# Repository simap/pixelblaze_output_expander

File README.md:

# USE THE APPROPRIATE BRANCH FOR YOUR HARDWARE VERSION!

* v1.x: https://github.com/simap/pixelblaze_output_expander/tree/master
* v2.x: https://github.com/simap/pixelblaze_output_expander/tree/v2.x
* v3.x: https://github.com/simap/pixelblaze_output_expander/tree/v3.x
* v4.x: this branch

The v3.x_spi and v3.x_apa102fastdata branches are variant firmwares for v3 boards. Both features are incorporated into v4.

Pixelblaze Output Expander Board
-------------------

This is a UART (serial) or SPI driven WS2811/WS2812/WS2813/NeoPixel and APA102/SK9822/DotStar driver. It receives frame data from another microcontroller, buffers it per channel, handles color ordering, and outputs up to 8 channels with level shifting to 5v. WS2812 and APA102 type LEDs can be mixed across channels.

Its primarily designed as an output expander for [Pixelblaze](https://www.tindie.com/products/12158/), but can be used with any microcontroller that can output 2Mbps serial or SPI. The UART input doesn't need to sustain 2Mbps, so this should work even for software serial implementations as long as the microcontroller is capable of outputting single characters at this rate.

See the companion [Arduino Library Driver](https://github.com/simap/pbDriverAdapter/) for use with Arduinos.

This branch is the firmware for the v4 boards, which are based on the RP2350. It also runs on RP2350 dev boards. The STM32 based v1 to v3 boards each have their own branch, linked above. The protocol is the same across all of them, the v4 boards add SPI input, larger buffers, and firmware updates over the data line.

| | v1 | v2 | v3 | v4 |
|---|---|---|---|---|
| MCU | STM32F070 | STM32F103 | STM32L432 | RP2350 |
| Input | UART 2Mbps | UART 2Mbps | UART 2Mbps | UART 2Mbps or SPI up to 20MHz |
| Bytes per channel | 720 | 2408 | 4808 | 16008 |
| WS2812 RGB pixels per channel | 240 | 802 | 1602 | 5336 |
| APA102 pixels per channel | no | 600 | 1200 | 4000 |

Input
-------------------

The data input pin takes either UART or SPI. Both receivers run all the time and the board picks whichever is active.

UART is 8N1 at 2Mbps, same as earlier boards. Only the data line is used.

SPI uses the clock input pin plus the data pin. There is no chip select. Mode 0 (clock idles low, data sampled on the rising edge), MSB first, any clock from 500kHz to 20MHz. The sender doesn't have to be continuous, bytes can arrive at any pace. If the clock stops for 10us in the middle of a byte, the partial byte is dropped and the receiver realigns on the next clock edge, so a sender should leave at least a 20us gap before each set of frames to recover from a lost or extra clock edge.

Once 8 bytes have arrived over SPI, the board switches to SPI and ignores the UART input (which sees the shared data line toggling at SPI rates). After 1 second with no SPI clock it switches back to UART.

Data Frame Format
-------------------

Frames start with a magic 4-byte sequence, followed by the channel ID (8 bits), then the command type (8 bits). Some commands have additional header/structs and payloads, finally every frame is ended with a 32-bit CRC that covers the entire frame (from magic to the last byte before CRC). All multi-byte fields are little endian.

```c
typedef struct {
	int8_t magic[4]; //"UPXL"
	uint8_t channel;
	uint8_t recordType; //set channel ws2812 opts+data, draw all
} PBFrameHeader;
```

Six commands are implemented. Four set a channel's configuration and buffer data, one draws all channels, and one carries a firmware update:

```c
enum {
	SET_CHANNEL_WS2812 = 1, DRAW_ALL, SET_CHANNEL_APA102_DATA, SET_CHANNEL_APA102_CLOCK, SET_CHANNEL_APA102_FAST_DATA, UPDATE
} RecordType;
```

The channel ID is part of the PBFrameHeader. Each board supports 8 channels, and has an additional 3 bits of address configured by cuttable jumpers on the underside of the board. Up to 64 channels can be on the same bus (8 boards w/ 8 channels each). The low 3 bits pick the channel on the board, the upper 3 bits must match the board's jumpers or the frame is ignored.

Any `SET_CHANNEL_*` command with a `pixels` count of 0 disables that channel.

### `SET_CHANNEL_WS2812`

The `SET_CHANNEL_WS2812` command frame header is immediately followed by a structure defining the configuration for that channel, and then followed by RGB or RGBW pixel data:

```c
typedef struct {
	uint8_t numElements; //3 (RGB) or 4 (RGBW)
	uint8_t redIndex :2, greenIndex :2, blueIndex :2, whiteIndex :2; //color orders, data on the line assumed to be RGB or RGBW
	uint16_t pixels;
} PBChannel;
```

In total:

```
PBFrameHeader + PBChannel + bytes[numElements * pixels] + CRC
```

Output is always at 800KHz.

### `SET_CHANNEL_APA102_DATA`

Sets a channel as the data line for APA102 type LEDs. Pixel data on the line is 4 bytes per pixel, RGB followed by a 5-bit brightness value. The color order bits work like WS2812. The start and end frames are added by the board, don't send them.

```c
typedef struct {
	uint32_t frequency; //clock rate in Hz
	uint8_t redIndex :2, greenIndex :2, blueIndex :2, unused :2;
	uint8_t reserved;
	uint16_t pixels;
} PBAPA102DataChannel;
```

In total:

```
PBFrameHeader + PBAPA102DataChannel + bytes[4 * pixels] + CRC
```

### `SET_CHANNEL_APA102_CLOCK`

Sets a channel as the clock line for APA102 type LEDs. Any number of data channels can share one clock channel, the clock runs for as many bits as the longest APA102 data channel on the board.

```c
typedef struct {
	uint32_t frequency; //clock rate in Hz
} PBAPA102ClockChannel;
```

In total:

```
PBFrameHeader + PBAPA102ClockChannel + CRC
```

The clock and all data channels are started together from the same clock divider so they stay in step. If channels ask for different frequencies, all APA102 channels on the board run at the lowest one requested, limited to the range 10KHz to 20MHz.

### `SET_CHANNEL_APA102_FAST_DATA`

Same as `SET_CHANNEL_APA102_DATA` but pixel data on the line is 2 bytes per pixel in RGB565, little endian. This halves the input bandwidth for more FPS. The board expands each pixel with a gamma curve, then uses the APA102's 5-bit brightness value to keep some dynamic range in the dark end.

```c
typedef struct {
	uint32_t frequency; //clock rate in Hz
	uint8_t redIndex :2, greenIndex :2, blueIndex :2, unused :2;
	uint8_t gammaTenths; //gamma * 10, 10 to 25 (1.0 to 2.5)
	uint16_t pixels;
} PBAPA102FastDataChannel;
```

In total:

```
PBFrameHeader + PBAPA102FastDataChannel + bytes[2 * pixels] + CRC
```

### `DRAW_ALL`

The `DRAW_ALL` command ignores the channel from the frame header, though it must still be followed by a CRC. All channels on the bus are drawn simultaneously when this command is received. This command ignores channel ID.

In total:

```
PBFrameHeader + CRC
```

### `UPDATE` (v4 boards)

Record type 6 carries a firmware update payload for the RP2350 based v4 boards. It is broadcast, so the channel byte is ignored. The frame header is followed by this header, then the payload, then the usual frame CRC:

```c
typedef struct {
	char key[64];     // hardware and payload type, NUL padded, e.g. "RP2350_ARM-2MB-standard-firmware"
	uint32_t length;  // payload bytes
	uint32_t crc;     // CRC32 of just key and length
} PBUpdate;
```

A board accepts the record only if the key is the one it was built with, so updates for other boards on the same bus are consumed and ignored. The header CRC keeps a magic sequence that happens to appear inside pixel data from locking up the parser on a bogus multi-megabyte payload. The payload is the `outputexpander.bin` from the build, which the pico-sdk seals with a SHA-256. See Firmware Updates below for what happens on the board.

Error Handling
-------------------

The firmware is designed to tolerate noise and data errors. Channel data is double-buffered. Each `SET_CHANNEL_*` frame is received into a spare buffer and only becomes the channel's pending frame once its CRC checks out. `DRAW_ALL` swaps every pending frame in and draws. A CRC mismatch throws the frame out and the channel keeps drawing its last good frame, so LEDs never see corrupted or zeroed data. Frames received during a draw go into a different buffer than the one being drawn.

The magic header provides a way to align frames in case of continuous transmission.

It's assumed that data will be more or less continuously flowing, and the reception code doesn't timeout if the input goes idle.

If part of a frame is received, it will wait for enough data to complete that frame, and eventually throw that out if the CRC doesn't match. If that is in the middle of another frame, it will discard data until the magic frame start sequence is found.

Frames with a bad or impossible header (unknown record type, more pixels than fit in a channel, zero frequency, etc) are skipped a byte at a time until the next magic sequence.

Timing Considerations
-------------------

Since channel data is double-buffered, you can send the next frame's channel data as soon as `DRAW_ALL` has been sent, while the previous frame is still going out to the LEDs.

A `DRAW_ALL` that arrives while a draw is still in progress is dropped. The same goes for a `DRAW_ALL` within 300us of the end of a WS2812 draw, since the LEDs need that time to latch. The channel data sent before it is kept and goes out on the next `DRAW_ALL`. WS2812 output takes 30us per RGB pixel (40us for RGBW) on the longest channel, plus the 300us latch, so for example 300 RGB pixels takes about 9.3ms and tops out around 107 FPS. APA102 takes 32 bits per pixel plus start and end frames at the configured clock rate.

Each channel only sends as many pixels as it was configured for, so a short channel finishes early and doesn't wait for the longest.

Status LEDs
-------------------

The status LED is on solid while frames are arriving, and breathes slowly when the input has been idle for a second. The draw LED is on while valid channel data and draw commands are both arriving.

Firmware Updates
-------------------

v4 boards can be updated over the data line with the `UPDATE` record. Flash is split into an A/B pair of 384KB slots with a partition table in the first sector. An update is written to whichever slot isn't running, then the board reboots into it. The bootrom checks the SHA-256 before running it, and falls back to the old slot if it doesn't check out, if power is lost mid-write, or if the new firmware never starts working.

The new firmware runs in try-before-you-buy mode. It commits itself (and the bootrom erases the old slot's header so the new one is preferred from then on) on the first frame it receives with a good CRC. Until then a reset goes back to the old firmware.

Updates are exact version installs. Downgrades are allowed. The only update that is skipped is one carrying the same image that is already running, compared by hash. A board gets about 384KB of RAM to hold the payload so that is the size limit. The firmware is currently about 36KB, so there is plenty of headroom.

While an update is being received the LED output stops and holds whatever was last drawn. A bad CRC on the update, or the input stopping mid-payload, reboots back into the running firmware with flash untouched.

Building
-------------------

The firmware builds with the pico-sdk (2.3.1) and CMake in the usual way with `cmake -B build && cmake --build build`. The build produces two images:

* The base image, `outputexpander.uf2` for BOOTSEL and `outputexpander_base.bin` for SWD. This is the partition table plus the firmware in slot A, with slot B cleared. Use it to prep a new board, recover a bricked one, or update manually. It overwrites whatever is on the board, partition table included. `flash_ab.sh` writes it over SWD.
* The update image, `outputexpander_update.bin`. This is the app firmware alone, built with the try-before-you-buy flag, and is the payload for the `UPDATE` record. Embed it in another microcontroller to bring attached expanders to a known version.

The base image isn't try-before-you-buy because the bootrom only starts a TBYB image after a flash update reboot, so one loaded over BOOTSEL or SWD would never run. `outputexpander.elf` and `outputexpander.bin` are the plain firmware on its own, for the debugger.

`make -C firmware/test run` builds and runs host tests for the parser and channel code.

Implementation
-------------------

Output uses one PIO state machine per channel, fed by its own DMA channel from the channel's buffer. Channels 0-3 are on PIO0 and 4-7 on PIO1, and all 8 state machines are enabled with a single register write so they start on the same clock. There is no bit transposing, each channel's buffer holds its pixels as 32-bit words with the first wire byte in the top byte and the PIO shifts them out MSB first.

The WS2812 program runs 20 PIO cycles per bit at 16MHz. The APA102 data program is 2 cycles per bit, and the APA102 clock program counts bits with the same divider, so clock and data stay aligned even on different PIO blocks.

Input DMA fills an 8KB ring buffer from UART0 and a second ring from a PIO SPI receiver on PIO2. The parser walks the rings, finds the magic, validates the header, and copies the payload out with a memory-to-memory DMA that has the CRC32 sniffer enabled, so the CPU never runs a CRC loop. Pixel data is converted to the output word format as it streams out of the ring.

Channel buffers come from a pool of 17: one being drawn and one pending per channel plus one receive target. The pool doubles as the RAM buffer for a firmware update payload.

Once set up, the CPU doesn't have to do anything while a draw is running, and the accuracy of the WS2812 signal is very good.

License Information
-------------------
The hardware files are released under [Creative Commons ShareAlike 4.0 International](https://creativecommons.org/licenses/by-sa/4.0/).

Distributed as-is; no warranty is given.

The ElectroMage logo and wizard character is excluded from this license.

The software is released under The MIT License.

The MIT License

Copyright (c) 2018-2026 Ben Hencke

Permission is hereby granted, free of charge, to any person obtaining a copy
of this software and associated documentation files (the "Software"), to deal
in the Software without restriction, including without limitation the rights
to use, copy, modify, merge, publish, distribute, sublicense, and/or sell
copies of the Software, and to permit persons to whom the Software is
furnished to do so, subject to the following conditions:

The above copyright notice and this permission notice shall be included in
all copies or substantial portions of the Software.

THE SOFTWARE IS PROVIDED "AS IS", WITHOUT WARRANTY OF ANY KIND, EXPRESS OR
IMPLIED, INCLUDING BUT NOT LIMITED TO THE WARRANTIES OF MERCHANTABILITY,
FITNESS FOR A PARTICULAR PURPOSE AND NONINFRINGEMENT. IN NO EVENT SHALL THE
AUTHORS OR COPYRIGHT HOLDERS BE LIABLE FOR ANY CLAIM, DAMAGES OR OTHER
LIABILITY, WHETHER IN AN ACTION OF CONTRACT, TORT OR OTHERWISE, ARISING FROM,
OUT OF OR IN CONNECTION WITH THE SOFTWARE OR THE USE OR OTHER DEALINGS IN
THE SOFTWARE.

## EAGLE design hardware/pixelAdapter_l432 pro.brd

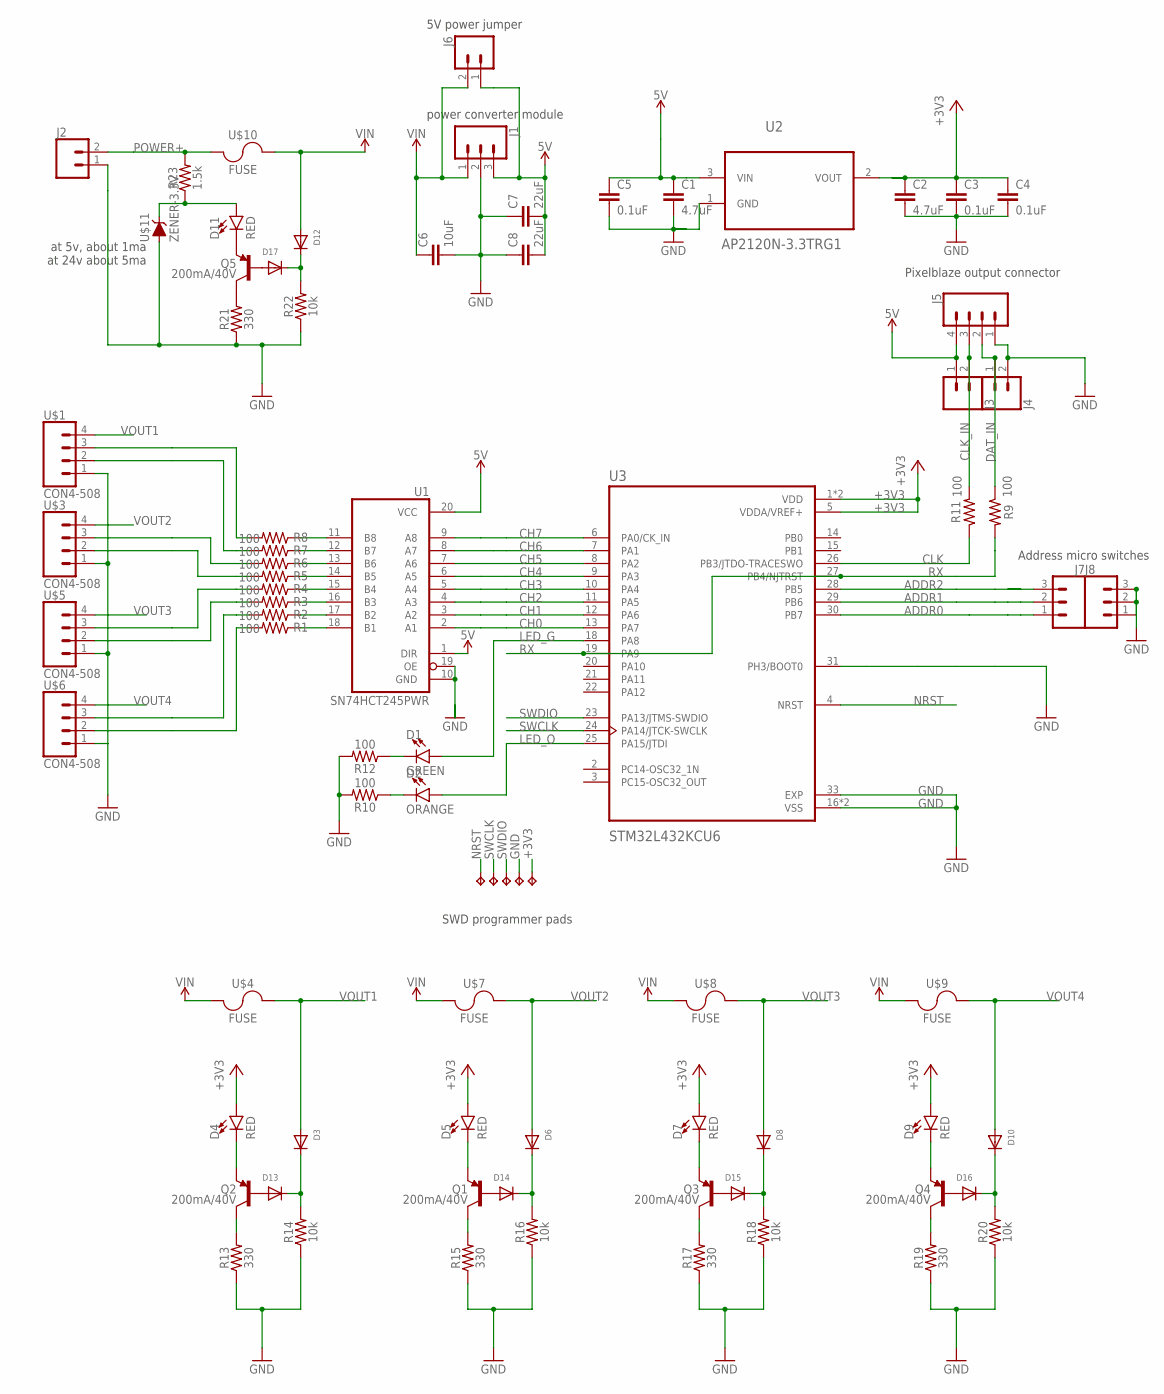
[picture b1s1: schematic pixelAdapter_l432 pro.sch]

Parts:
C1, C2: 4.7uF; 0603
C3, C4, C5: 0.1uF; 0603
C6: 10uF; 1210
C7, C8: 22uF; 1210
D1: GREEN; LED-0603
D2: ORANGE; LED-0603
D3, D6, D8, D10, D12, D13, D14, D15, D16, D17: DIODESOD-123; SOD-123
D4, D5, D7, D9, D11: RED; LED-0603
J1: CONN_03; 1X03
J2, J3, J4: CONN_025MM; SCREWTERMINAL-5MM-2
J5: CONN_04LOCK; 1X04_LOCK
J6: CONN_02; 1X02
J7, J8: CONN_03LOCK; 1X03_LOCK
Q1, Q2, Q3, Q4, Q5: 200mA/40V; SOT23-3
R1, R2, R3, R4, R5, R6, R7, R8, R9, R10, R11, R12: 100; 0603
R13, R15, R17, R19, R21: 330; 0603
R14, R16, R18, R20, R22: 10k; 0603
R23: 1.5k; 0603
TP1, TP2, TP3, TP4, TP5: TPTP20SQ; TP20SQ
U1: SN74HCT245PWR; TSSOP20
U2: AP2120N-3.3TRG1; SOT95P237X112-3N
U3: STM32L432KCU6; QFN50P500X500X60-33N
U$1, U$3, U$5, U$6: CON4-508
U$4, U$7, U$8, U$9, U$10: FUSE; KEYSTONE-3586-FUSEHOLDER
U$11: ZENER-3.3V; SOD-123FL

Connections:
5V: C1.1, C5.1, C7.2, C8.2, J1.3, J3.1, J5.4, J6.1, U1.1 (DIR), U1.20 (VCC), U2.3 (VIN)
+3V3: C2.1, C3.1, C4.1, D4.A, D5.A, D7.A, D9.A, TP4.TP, U2.2 (VOUT), U3.1 (VDD), U3.5 (VDDA/VREF+), U3.17 (VDD)
ADDR0: J7.1, U3.30 (PB7)
ADDR1: J7.2, U3.29 (PB6)
ADDR2: J7.3, U3.28 (PB5)
CH0: U1.2 (A1), U3.13 (PA7)
CH1: U1.3 (A2), U3.12 (PA6)
CH2: U1.4 (A3), U3.11 (PA5)
CH3: U1.5 (A4), U3.10 (PA4)
CH4: U1.6 (A5), U3.9 (PA3)
CH5: U1.7 (A6), U3.8 (PA2)
CH6: U1.8 (A7), U3.7 (PA1)
CH7: U1.9 (A8), U3.6 (PA0/CK_IN)
CLK: R11.1, U3.26 (PB3/JTDO-TRACESWO)
CLK_IN: J3.2, J5.3, R11.2
DAT_IN: J4.1, J5.2, R9.1
GND: C1.2, C2.2, C3.2, C4.2, C5.2, C6.2, C7.1, C8.1, J1.2, J2.1, J4.2, J5.1, J8.1, J8.2, J8.3, R10.2, R12.2, R13.1, R14.1, R15.1, R16.1, R17.1, R18.1, R19.1, R20.1, R21.1, R22.1, TP3.TP, U1.10 (GND), U1.19 (OE), U2.1 (GND), U3.16 (VSS), U3.31 (PH3/BOOT0), U3.32 (VSS), U3.33 (EXP), U$1.1, U$3.1, U$5.1, U$6.1, U$11.A
LED0: R1.2, U$6.2
LED1: R2.2, U$6.3
LED2: R3.2, U$5.2
LED3: R4.2, U$5.3
LED4: R5.2, U$3.2
LED5: R6.2, U$3.3
LED6: R7.2, U$1.2
LED7: R8.2, U$1.3
LED_G: D1.A, U3.18 (PA8)
LED_O: D2.A, U3.25 (PA15/JTDI)
unnamed: D17.A, Q5.1 (B)
unnamed: D1.C, R12.1
unnamed: D12.C, D17.C, R22.2
unnamed: D3.C, D13.C, R14.2
unnamed: D4.C, Q2.2 (E)
unnamed: D11.C, Q5.2 (E)
unnamed: Q2.3 (C), R13.2
unnamed: Q5.3 (C), R21.2
unnamed: D6.C, D14.C, R16.2
unnamed: D5.C, Q1.2 (E)
unnamed: Q1.3 (C), R15.2
unnamed: R1.1, U1.18 (B1)
unnamed: R2.1, U1.17 (B2)
unnamed: R3.1, U1.16 (B3)
unnamed: R4.1, U1.15 (B4)
unnamed: R5.1, U1.14 (B5)
unnamed: R6.1, U1.13 (B6)
unnamed: R7.1, U1.12 (B7)
unnamed: R8.1, U1.11 (B8)
unnamed: D11.A, R23.1, U$11.C
unnamed: D2.C, R10.1
unnamed: D8.C, D15.C, R18.2
unnamed: D7.C, Q3.2 (E)
unnamed: Q3.3 (C), R17.2
unnamed: D13.A, Q2.1 (B)
unnamed: D10.C, D16.C, R20.2
unnamed: D9.C, Q4.2 (E)
unnamed: Q4.3 (C), R19.2
unnamed: D14.A, Q1.1 (B)
unnamed: D15.A, Q3.1 (B)
unnamed: D16.A, Q4.1 (B)
NRST: TP5.TP, U3.4 (NRST)
POWER+: J2.2, R23.2, U$10.A1 (1), U$10.A2 (1), U$10.A3 (1)
RX: R9.2, U3.19 (PA9), U3.27 (PB4/NJTRST)
SWCLK: TP1.TP, U3.24 (PA14/JTCK-SWCLK)
SWDIO: TP2.TP, U3.23 (PA13/JTMS-SWDIO)
VIN: C6.1, D12.A, J1.1, J6.2, U$4.A1 (1), U$4.A2 (1), U$4.A3 (1), U$7.A1 (1), U$7.A2 (1), U$7.A3 (1), U$8.A1 (1), U$8.A2 (1), U$8.A3 (1), U$9.A1 (1), U$9.A2 (1), U$9.A3 (1), U$10.B1 (2), U$10.B2 (2), U$10.B3 (2)
VOUT1: D3.A, U$1.4, U$4.B1 (2), U$4.B2 (2), U$4.B3 (2)
VOUT2: D6.A, U$3.4, U$7.B1 (2), U$7.B2 (2), U$7.B3 (2)
VOUT3: D8.A, U$5.4, U$8.B1 (2), U$8.B2 (2), U$8.B3 (2)
VOUT4: D10.A, U$6.4, U$9.B1 (2), U$9.B2 (2), U$9.B3 (2)

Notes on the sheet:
Pixelblaze output connector
SWD programmer pads
Address micro switches
at 5v, about 1ma at 24v about 5ma
power converter module
5V power jumper

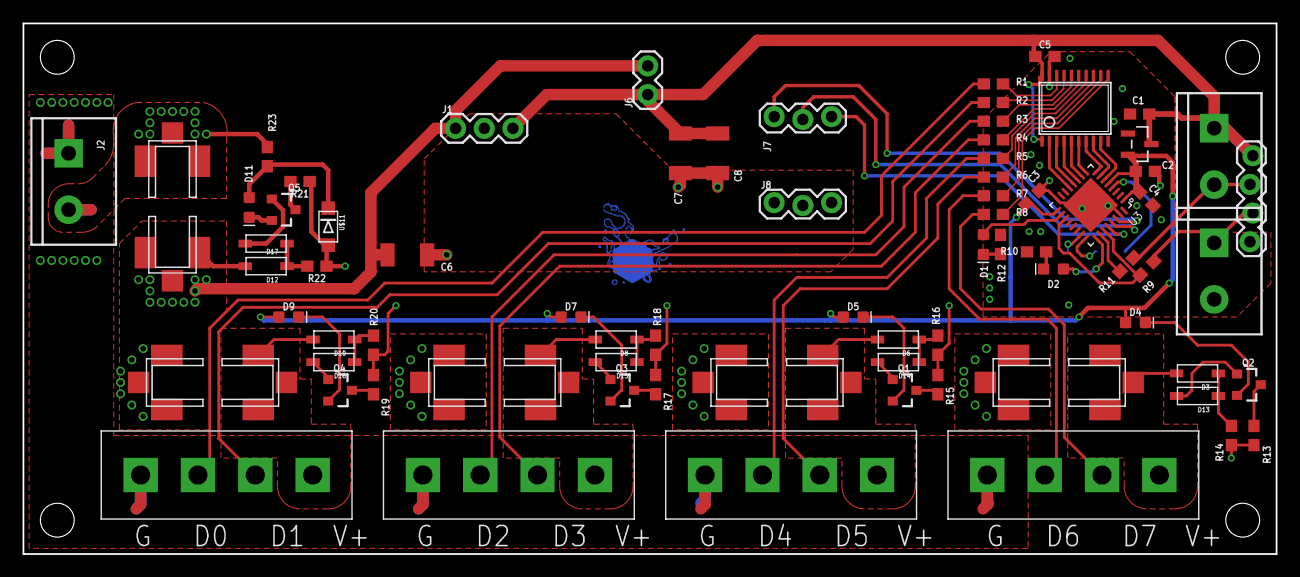
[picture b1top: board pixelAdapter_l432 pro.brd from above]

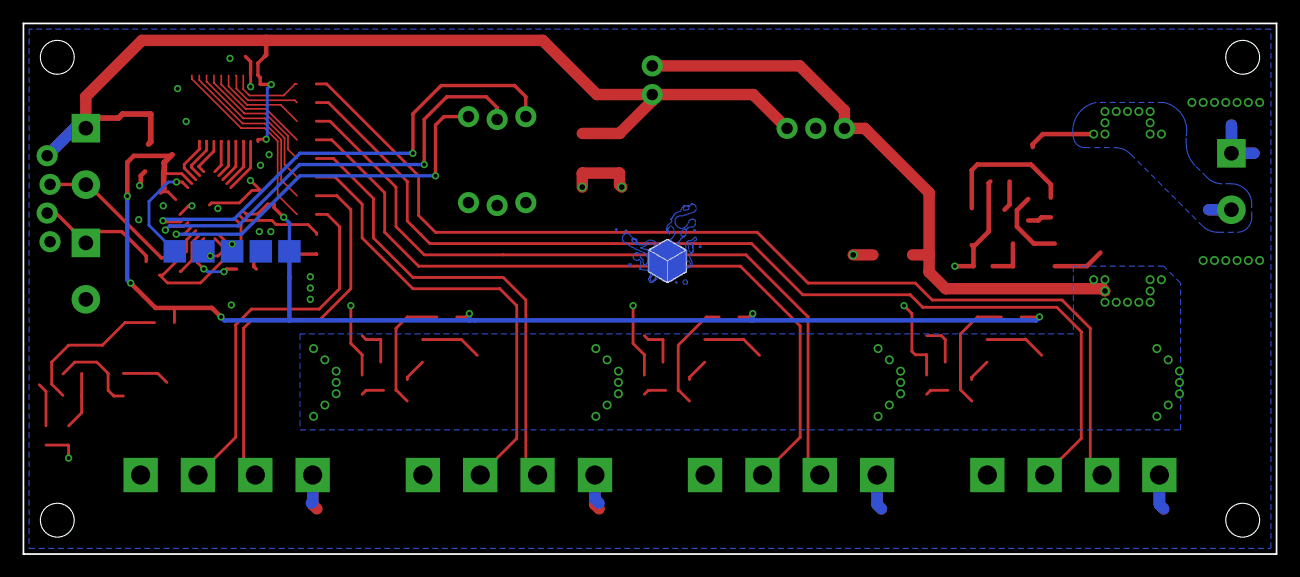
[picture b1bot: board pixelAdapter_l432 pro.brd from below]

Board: 2 copper layers, 111.0 x 47.0 mm, 80 parts (6 on the bottom side), 68 nets.

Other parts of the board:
U$2: ELECTRO_MAGE_PCB4_PIXEL_2#PNG

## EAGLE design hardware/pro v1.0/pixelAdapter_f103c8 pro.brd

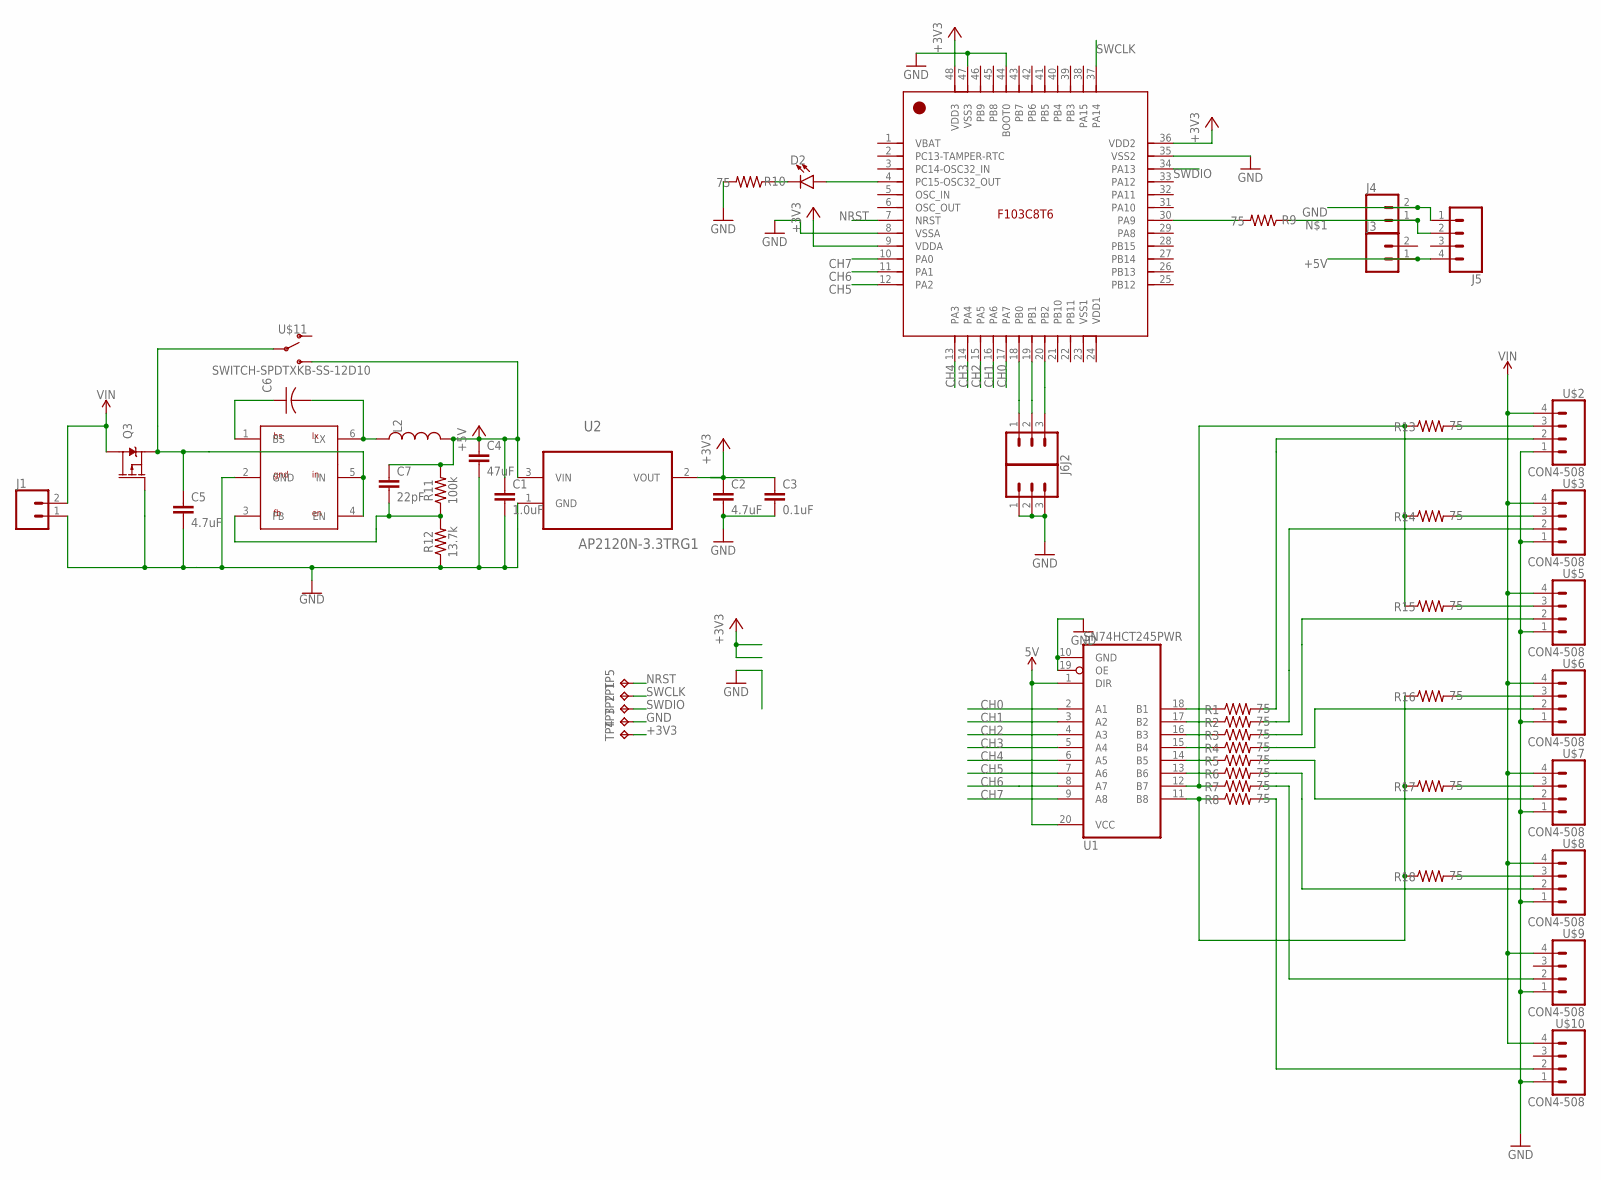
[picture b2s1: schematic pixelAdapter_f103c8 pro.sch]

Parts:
C1: 1.0uF; 0603
C2: 4.7uF; 0603
C3: 0.1uF; 0603
C4: 47uF; 1206
C5: 4.7uF; 1206
C6: 0.1uF; C0402K
C7: 22pF; 0603
D2: LED0603; LED-0603
J1, J3, J4: CONN_025MM; SCREWTERMINAL-5MM-2
J2, J6: CONN_03LOCK; 1X03_LOCK
J5: CONN_04LOCK; 1X04_LOCK
L2: INDUCTOR3030; INDUCTOR-3030
Q3: 2.5A/30V/105mΩ; SOT23-3
R1, R2, R3, R4, R5, R6, R7, R8, R9, R10, R13, R14, R15, R16, R17, R18: 75; 0603
R11: 100k; 0603
R12: 13.7k; 0603
TP1, TP2, TP3, TP4, TP5: TPTP20SQ; TP20SQ
U1: SN74HCT245PWR; TSSOP20
U2: AP2120N-3.3TRG1; SOT95P237X112-3N
U$1: STM32F103C8T6; LQFP48_7X7MM_0.5MMPP
U$2, U$3, U$5, U$6, U$7, U$8, U$9, U$10: CON4-508
U$4: SY8120B1ABC; SOT23-6
U$11: SWITCH-SPDTXKB-SS-12D10; SWITCH-XKB-SS-12D10

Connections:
+3V3: C2.1, C3.1, TP4.TP, U2.2 (VOUT), U$1.9 (VDDA), U$1.36 (VDD2), U$1.48 (VDD3)
+5V: C1.1, C4.1, C7.1, J3.1, J5.4, L2.P$2 (2), R11.2, U1.1 (DIR), U1.20 (VCC), U2.3 (VIN), U$11.P$3 (S)
ADDR0: J2.1, U$1.18 (PB0)
ADDR1: J2.2, U$1.19 (PB1)
ADDR2: J2.3, U$1.20 (PB2)
CH0: U1.2 (A1), U$1.17 (PA7)
CH1: U1.3 (A2), U$1.16 (PA6)
CH2: U1.4 (A3), U$1.15 (PA5)
CH3: U1.5 (A4), U$1.14 (PA4)
CH4: U1.6 (A5), U$1.13 (PA3)
CH5: U1.7 (A6), U$1.12 (PA2)
CH6: U1.8 (A7), U$1.11 (PA1)
CH7: U1.9 (A8), U$1.10 (PA0)
GND: C1.2, C2.2, C3.2, C4.2, C5.2, J1.1, J4.2, J5.1, J6.1, J6.2, J6.3, Q3.1 (G), R10.2, R12.1, TP3.TP, U1.10 (GND), U1.19 (OE), U2.1 (GND), U$1.8 (VSSA), U$1.35 (VSS2), U$1.44 (BOOT0), U$1.47 (VSS3), U$2.1, U$3.1, U$4.2 (GND), U$5.1, U$6.1, U$7.1, U$8.1, U$9.1, U$10.1
LED0: R1.2, U$2.2
LED1: R2.2, U$3.2
LED2: R3.2, U$5.2
LED3: R4.2, U$6.2
LED4: R5.2, U$7.2
LED5: R6.2, U$8.2
LED6: R7.2, U$9.2
LED7: R8.2, U$10.2
LEDS0: R1.1, U1.18 (B1)
LEDS1: R2.1, U1.17 (B2)
LEDS2: R3.1, U1.16 (B3)
LEDS3: R4.1, U1.15 (B4)
LEDS4: R5.1, U1.14 (B5)
LEDS5: R6.1, U1.13 (B6)
LEDS6: R7.1, R13.1, R14.1, R15.1, U1.12 (B7)
LEDS7: R8.1, R16.1, R17.1, R18.1, U1.11 (B8)
unnamed: J4.1, J5.2, R9.1
unnamed: D2.A, U$1.4 (PC15-OSC32_OUT)
unnamed: R13.2, U$2.3
unnamed: R14.2, U$3.3
unnamed: C6.1, U$4.1 (BS)
unnamed: C6.2, L2.P$1 (1), U$4.6 (LX)
unnamed: C7.2, R11.1, R12.2, U$4.3 (FB)
unnamed: R15.2, U$5.3
unnamed: R16.2, U$6.3
unnamed: D2.C, R10.1
unnamed: R17.2, U$7.3
unnamed: R18.2, U$8.3
NRST: TP5.TP, U$1.7 (NRST)
RX: R9.2, U$1.30 (PA9)
SWCLK: TP1.TP, U$1.37 (PA14)
SWDIO: TP2.TP, U$1.34 (PA13)
VIN: J1.2, Q3.3 (D), U$2.4, U$3.4, U$5.4, U$6.4, U$7.4, U$8.4, U$9.4, U$10.4
VIN1: C5.1, Q3.2 (S), U$4.4 (EN), U$4.5 (IN), U$11.P$2

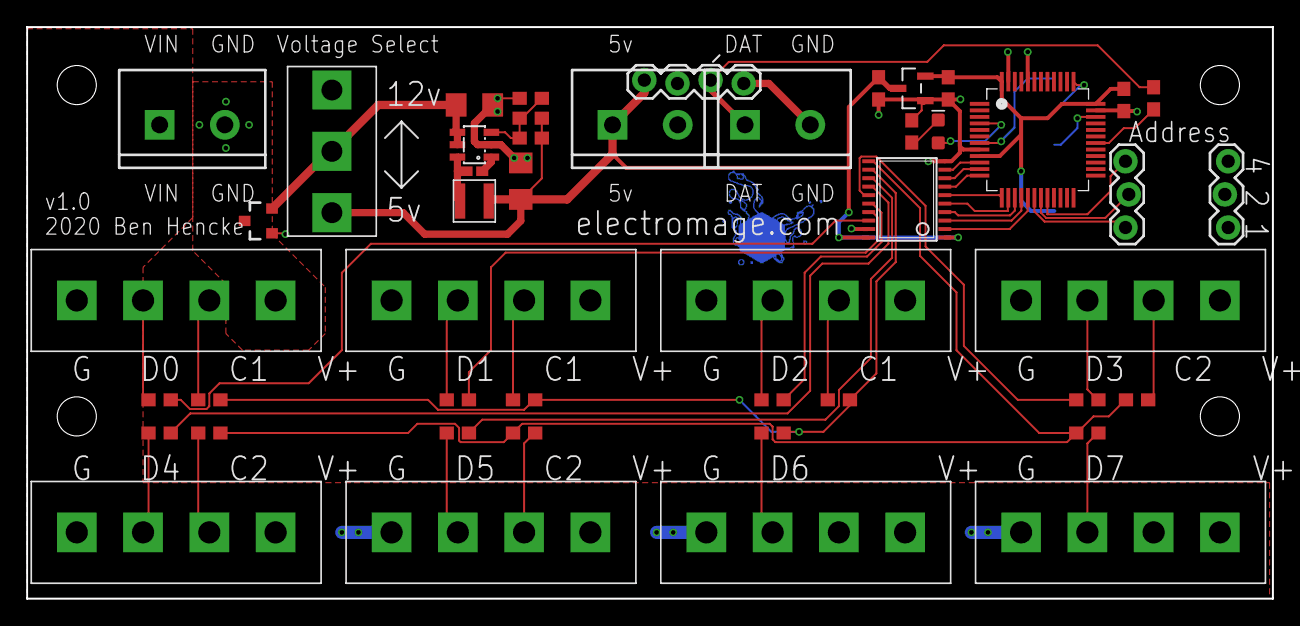
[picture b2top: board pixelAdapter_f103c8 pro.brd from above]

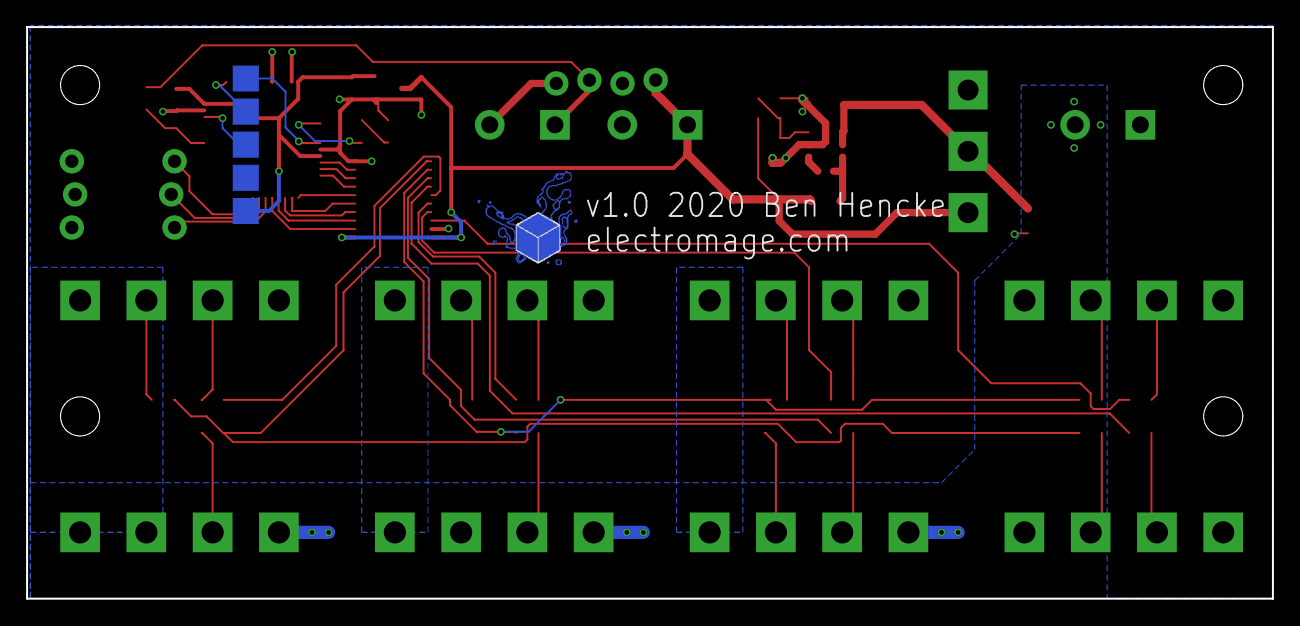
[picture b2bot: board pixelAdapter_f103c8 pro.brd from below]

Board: 4 copper layers, 95.5 x 43.8 mm, 53 parts (6 on the bottom side), 48 nets.

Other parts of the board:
U$12: ELECTRO_MAGE_PCB4_PIXEL_2#PNG

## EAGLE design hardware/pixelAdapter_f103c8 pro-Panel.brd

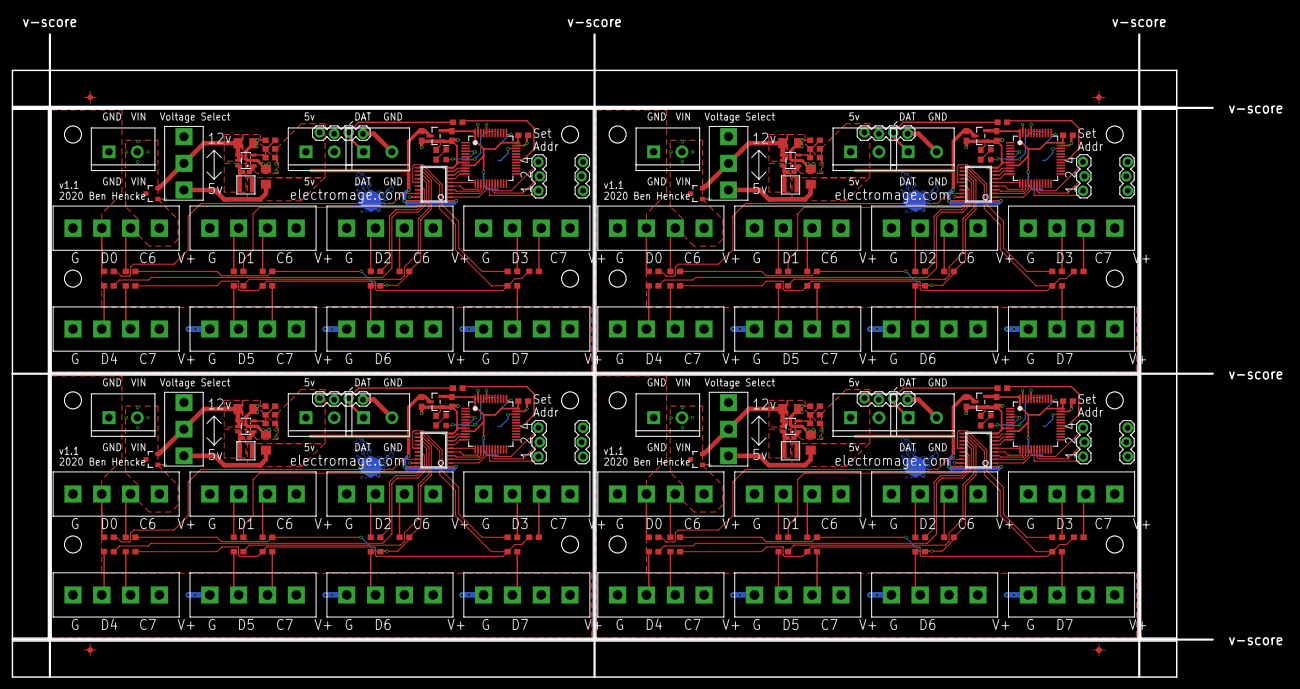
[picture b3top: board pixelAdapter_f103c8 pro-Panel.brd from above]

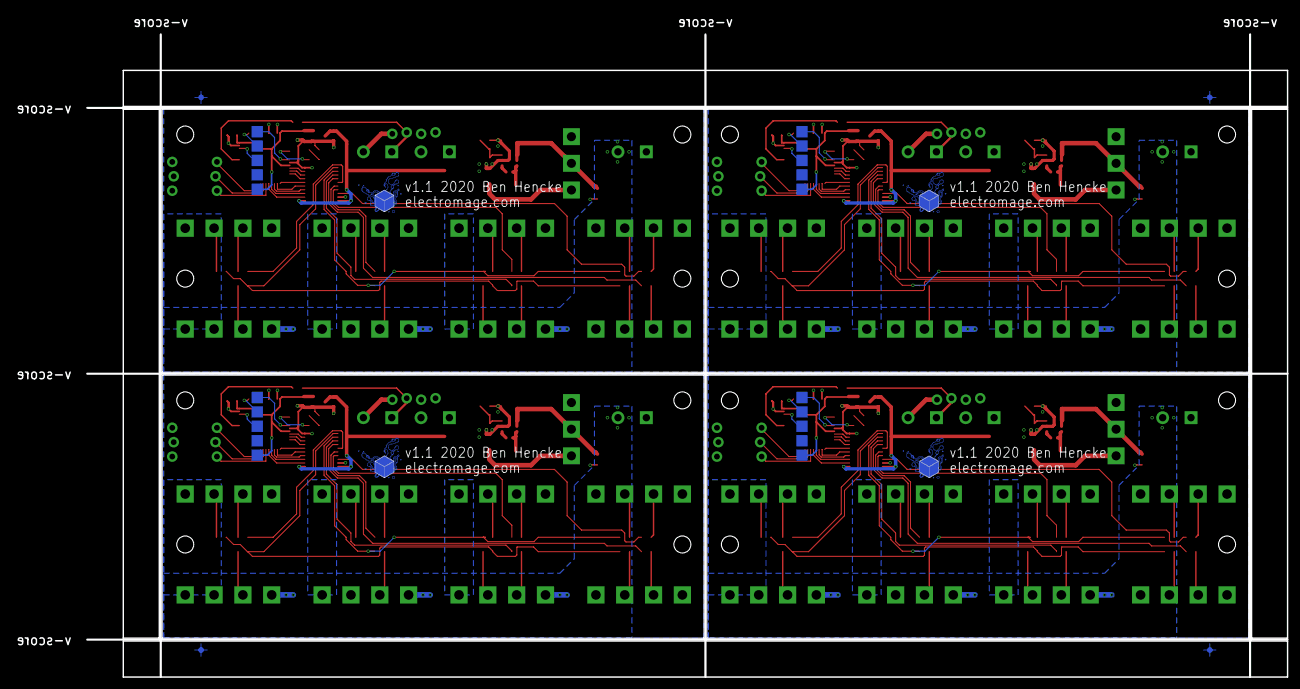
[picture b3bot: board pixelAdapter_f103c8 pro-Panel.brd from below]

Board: 2 copper layers, 211.6 x 113.3 mm, 220 parts (28 on the bottom side), 192 nets.

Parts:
C1, C14, C21, C28: 1.0uF; 0603
C2, C9, C16, C23: 4.7uF; 0603
C3, C8, C15, C22: 0.1uF; 0603
C4, C12, C19, C26: 47uF; 1206
C5, C10, C17, C24: 4.7uF; 1206
C6, C13, C20, C27: 0.1uF; C0402K
C7, C11, C18, C25: 22pF; 0603
D1, D2, D3, D4: LED-0603
E$1, E$2, E$3, E$4, E$5, E$6, E$7, E$8: BENSFIDUCIAL-SMALL
J1, J3, J4, J7, J8, J10, J13, J14, J16, J19, J20, J22: SCREWTERMINAL-5MM-2
J2, J6, J11, J12, J17, J18, J23, J24: 1X03_LOCK
J5, J9, J15, J21: 1X04_LOCK
L1, L2, L3, L4: INDUCTOR3030; INDUCTOR-3030
Q1, Q2, Q3, Q4: 2.5A/30V/105mΩ; SOT23-3
R1, R2, R3, R4, R5, R6, R7, R8, R9, R10, R13, R14, R15, R16, R17, R18, R19, R20, R21, R22, R23, R24, R25, R26, R27, R28, R31, R32, R33, R34, R35, R36, R37, R38, R39, R40, R41, R42, R43, R44, R45, R46, R49, R50, R51, R52, R53, R54, R55, R56, R57, R58, R59, R60, R61, R62, R63, R64, R67, R68, R69, R70, R71, R72: 75; 0603
R11, R29, R47, R65: 100k; 0603
R12, R30, R48, R66: 13.7k; 0603
TP1, TP2, TP3, TP4, TP5, TP6, TP7, TP8, TP9, TP10, TP11, TP12, TP13, TP14, TP15, TP16, TP17, TP18, TP19, TP20: TPTP20SQ; TP20SQ
U1, U3, U5, U7: SN74HCT245PWR; TSSOP20
U2, U4, U6, U8: AP2120N-3.3TRG1; SOT95P237X112-3N
U$1, U$13, U$25, U$37: STM32F103C8T6; LQFP48_7X7MM_0.5MMPP
U$2, U$3, U$5, U$6, U$7, U$8, U$9, U$10, U$15, U$16, U$17, U$18, U$19, U$20, U$21, U$22, U$27, U$28, U$29, U$30, U$31, U$32, U$33, U$34, U$39, U$40, U$41, U$42, U$43, U$44, U$45, U$46: CON4-508
U$4, U$14, U$26, U$38: SY8120B1ABC; SOT23-6
U$11, U$23, U$35, U$47: SWITCH-SPDTXKB-SS-12D10; SWITCH-XKB-SS-12D10
U$12, U$24, U$36, U$48: ELECTRO_MAGE_PCB4_PIXEL_2#PNG

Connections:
+3V1: C8.1, C9.1, TP9.TP, U4.2, U$13.9, U$13.36, U$13.48
+3V2: C15.1, C16.1, TP14.TP, U6.2, U$25.9, U$25.36, U$25.48
+3V3: C2.1, C3.1, TP4.TP, U2.2, U$1.9, U$1.36, U$1.48
+3V4: C22.1, C23.1, TP19.TP, U8.2, U$37.9, U$37.36, U$37.48
+5V: C1.1, C4.1, C7.1, J3.1, J5.4, L2.P$2, R11.2, U1.1, U1.20, U2.3, U$11.P$3
+5V1: C11.1, C12.1, C14.1, J7.1, J9.4, L1.P$2, R29.2, U3.1, U3.20, U4.3, U$23.P$3
+5V2: C18.1, C19.1, C21.1, J13.1, J15.4, L3.P$2, R47.2, U5.1, U5.20, U6.3, U$35.P$3
+5V3: C25.1, C26.1, C28.1, J19.1, J21.4, L4.P$2, R65.2, U7.1, U7.20, U8.3, U$47.P$3
ADDR0: J2.1, U$1.18
ADDR1: J2.2, U$1.19
ADDR2: J2.3, U$1.20
ADDR3: J11.1, U$13.18
ADDR4: J11.2, U$13.19
ADDR5: J11.3, U$13.20
ADDR6: J17.1, U$25.18
ADDR7: J17.2, U$25.19
ADDR8: J17.3, U$25.20
ADDR9: J23.1, U$37.18
ADDR10: J23.2, U$37.19
ADDR11: J23.3, U$37.20
CH0: U1.2, U$1.17
CH1: U1.3, U$1.16
CH2: U1.4, U$1.15
CH3: U1.5, U$1.14
CH4: U1.6, U$1.13
CH5: U1.7, U$1.12
CH6: U1.8, U$1.11
CH7: U1.9, U$1.10
CH8: U3.9, U$13.10
CH9: U3.8, U$13.11
CH10: U3.7, U$13.12
CH11: U3.2, U$13.17
CH12: U3.3, U$13.16
CH13: U3.4, U$13.15
CH14: U3.5, U$13.14
CH15: U3.6, U$13.13
CH16: U5.9, U$25.10
CH17: U5.8, U$25.11
CH18: U5.7, U$25.12
CH19: U5.2, U$25.17
CH20: U5.3, U$25.16
CH21: U5.4, U$25.15
CH22: U5.5, U$25.14
CH23: U5.6, U$25.13
CH24: U7.9, U$37.10
CH25: U7.8, U$37.11
CH26: U7.7, U$37.12
CH27: U7.2, U$37.17
CH28: U7.3, U$37.16
CH29: U7.4, U$37.15
CH30: U7.5, U$37.14
CH31: U7.6, U$37.13
GND: C1.2, C2.2, C3.2, C4.2, C5.2, J1.1, J4.2, J5.1, J6.1, J6.2, J6.3, Q3.1, R10.2, R12.1, TP3.TP, U1.10, U1.19, U2.1, U$1.8, U$1.35, U$1.44, U$1.47, U$2.1, U$3.1, U$4.2, U$5.1, U$6.1, U$7.1, U$8.1, U$9.1, U$10.1
GND1: C8.2, C9.2, C10.2, C12.2, C14.2, J8.2, J9.1, J10.1, J12.1, J12.2, J12.3, Q1.1, R27.2, R30.1, TP8.TP, U3.10, U3.19, U4.1, U$13.8, U$13.35, U$13.44, U$13.47, U$14.2, U$15.1, U$16.1, U$17.1, U$18.1, U$19.1, U$20.1, U$21.1, U$22.1
GND2: C15.2, C16.2, C17.2, C19.2, C21.2, J14.2, J15.1, J16.1, J18.1, J18.2, J18.3, Q2.1, R45.2, R48.1, TP13.TP, U5.10, U5.19, U6.1, U$25.8, U$25.35, U$25.44, U$25.47, U$26.2, U$27.1, U$28.1, U$29.1, U$30.1, U$31.1, U$32.1, U$33.1, U$34.1
GND3: C22.2, C23.2, C24.2, C26.2, C28.2, J20.2, J21.1, J22.1, J24.1, J24.2, J24.3, Q4.1, R63.2, R66.1, TP18.TP, U7.10, U7.19, U8.1, U$37.8, U$37.35, U$37.44, U$37.47, U$38.2, U$39.1, U$40.1, U$41.1, U$42.1, U$43.1, U$44.1, U$45.1, U$46.1
LED0: R1.2, U$2.2
LED1: R2.2, U$3.2
LED2: R3.2, U$5.2
LED3: R4.2, U$6.2
LED4: R5.2, U$7.2
LED5: R6.2, U$8.2
LED6: R7.2, U$9.2
LED7: R8.2, U$10.2
LED8: R24.2, U$20.2
LED9: R23.2, U$19.2
LED10: R22.2, U$18.2
LED11: R21.2, U$17.2
LED12: R20.2, U$16.2
LED13: R19.2, U$15.2
LED14: R25.2, U$21.2
LED15: R26.2, U$22.2
LED16: R42.2, U$32.2
LED17: R41.2, U$31.2
LED18: R40.2, U$30.2
LED19: R39.2, U$29.2
LED20: R38.2, U$28.2
LED21: R37.2, U$27.2
LED22: R43.2, U$33.2
LED23: R44.2, U$34.2
LED24: R60.2, U$44.2
LED25: R59.2, U$43.2
LED26: R58.2, U$42.2
LED27: R57.2, U$41.2
LED28: R56.2, U$40.2
LED29: R55.2, U$39.2
LED30: R61.2, U$45.2
LED31: R62.2, U$46.2
LEDS0: R1.1, U1.18
LEDS1: R2.1, U1.17
LEDS2: R3.1, U1.16
LEDS3: R4.1, U1.15
LEDS4: R5.1, U1.14
LEDS5: R6.1, U1.13
LEDS6: R7.1, R13.1, R14.1, R15.1, U1.12
LEDS7: R8.1, R16.1, R17.1, R18.1, U1.11
LEDS8: R19.1, U3.18
LEDS9: R20.1, U3.17
LEDS10: R21.1, U3.16
LEDS11: R22.1, U3.15
LEDS12: R23.1, U3.14
LEDS13: R24.1, U3.13
LEDS14: R25.1, R31.1, R32.1, R33.1, U3.12
LEDS15: R26.1, R34.1, R35.1, R36.1, U3.11
LEDS16: R37.1, U5.18
LEDS17: R38.1, U5.17
LEDS18: R39.1, U5.16
LEDS19: R40.1, U5.15
LEDS20: R41.1, U5.14
LEDS21: R42.1, U5.13
LEDS22: R43.1, R49.1, R50.1, R51.1, U5.12
LEDS23: R44.1, R52.1, R53.1, R54.1, U5.11
LEDS24: R55.1, U7.18
LEDS25: R56.1, U7.17
LEDS26: R57.1, U7.16
LEDS27: R58.1, U7.15
LEDS28: R59.1, U7.14
LEDS29: R60.1, U7.13
LEDS30: R61.1, R67.1, R68.1, R69.1, U7.12
LEDS31: R62.1, R70.1, R71.1, R72.1, U7.11
unnamed: J4.1, J5.2, R9.1
unnamed: D1.C, R27.1
unnamed: D2.A, U$1.4
unnamed: J8.1, J9.2, R28.1
unnamed: D1.A, U$13.4
unnamed: R13.2, U$2.3
unnamed: R14.2, U$3.3
unnamed: C6.1, U$4.1
unnamed: C6.2, L2.P$1, U$4.6
unnamed: C7.2, R11.1, R12.2, U$4.3
unnamed: R15.2, U$5.3
unnamed: C13.1, U$14.1
unnamed: C13.2, L1.P$1, U$14.6
unnamed: C11.2, R29.1, R30.2, U$14.3
unnamed: R31.2, U$15.3
unnamed: R32.2, U$16.3
unnamed: R33.2, U$17.3
unnamed: R34.2, U$18.3
unnamed: R35.2, U$19.3
unnamed: R16.2, U$6.3
unnamed: D2.C, R10.1
unnamed: R17.2, U$7.3
unnamed: R18.2, U$8.3
unnamed: R36.2, U$20.3
unnamed: D3.C, R45.1
unnamed: J14.1, J15.2, R46.1
unnamed: D3.A, U$25.4
unnamed: C20.1, U$26.1
unnamed: C20.2, L3.P$1, U$26.6
unnamed: C18.2, R47.1, R48.2, U$26.3
unnamed: R49.2, U$27.3
unnamed: R50.2, U$28.3
unnamed: R51.2, U$29.3
unnamed: R52.2, U$30.3
unnamed: R53.2, U$31.3
unnamed: R54.2, U$32.3
unnamed: D4.C, R63.1
unnamed: J20.1, J21.2, R64.1
unnamed: D4.A, U$37.4
unnamed: C27.1, U$38.1
unnamed: C27.2, L4.P$1, U$38.6
unnamed: C25.2, R65.1, R66.2, U$38.3
unnamed: R67.2, U$39.3
unnamed: R68.2, U$40.3
unnamed: R69.2, U$41.3
unnamed: R70.2, U$42.3
unnamed: R71.2, U$43.3
unnamed: R72.2, U$44.3
NRST: TP5.TP, U$1.7
NRST1: TP10.TP, U$13.7
NRST2: TP15.TP, U$25.7
NRST3: TP20.TP, U$37.7
RX: R9.2, U$1.30
RX1: R28.2, U$13.30
RX2: R46.2, U$25.30
RX3: R64.2, U$37.30
SWCLK: TP1.TP, U$1.37
SWCLK1: TP6.TP, U$13.37
SWCLK2: TP11.TP, U$25.37
SWCLK3: TP16.TP, U$37.37
SWDIO: TP2.TP, U$1.34
SWDIO1: TP7.TP, U$13.34
SWDIO2: TP12.TP, U$25.34
SWDIO3: TP17.TP, U$37.34
VIN: J1.2, Q3.3, U$2.4, U$3.4, U$5.4, U$6.4, U$7.4, U$8.4, U$9.4, U$10.4
VIN1: C5.1, Q3.2, U$4.4, U$4.5, U$11.P$2
VIN2: J10.2, Q1.3, U$15.4, U$16.4, U$17.4, U$18.4, U$19.4, U$20.4, U$21.4, U$22.4
VIN3: C10.1, Q1.2, U$14.4, U$14.5, U$23.P$2
VIN4: J16.2, Q2.3, U$27.4, U$28.4, U$29.4, U$30.4, U$31.4, U$32.4, U$33.4, U$34.4
VIN5: C17.1, Q2.2, U$26.4, U$26.5, U$35.P$2
VIN6: J22.2, Q4.3, U$39.4, U$40.4, U$41.4, U$42.4, U$43.4, U$44.4, U$45.4, U$46.4
VIN7: C24.1, Q4.2, U$38.4, U$38.5, U$47.P$2

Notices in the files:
hardware/pixelAdapter_l432 pro.brd:
v3.1 ©2021
hardware/pixelAdapter_l432-Panel-v3.0.brd:
v3.0 ©2021
v3.0 ©2021 Ben Hencke
parts and their libraries:
SparkFun-Capacitors: Licensing: Creative Commons ShareAlike 4.0 International - https://creativecommons.org/licenses/by-sa/4.0
